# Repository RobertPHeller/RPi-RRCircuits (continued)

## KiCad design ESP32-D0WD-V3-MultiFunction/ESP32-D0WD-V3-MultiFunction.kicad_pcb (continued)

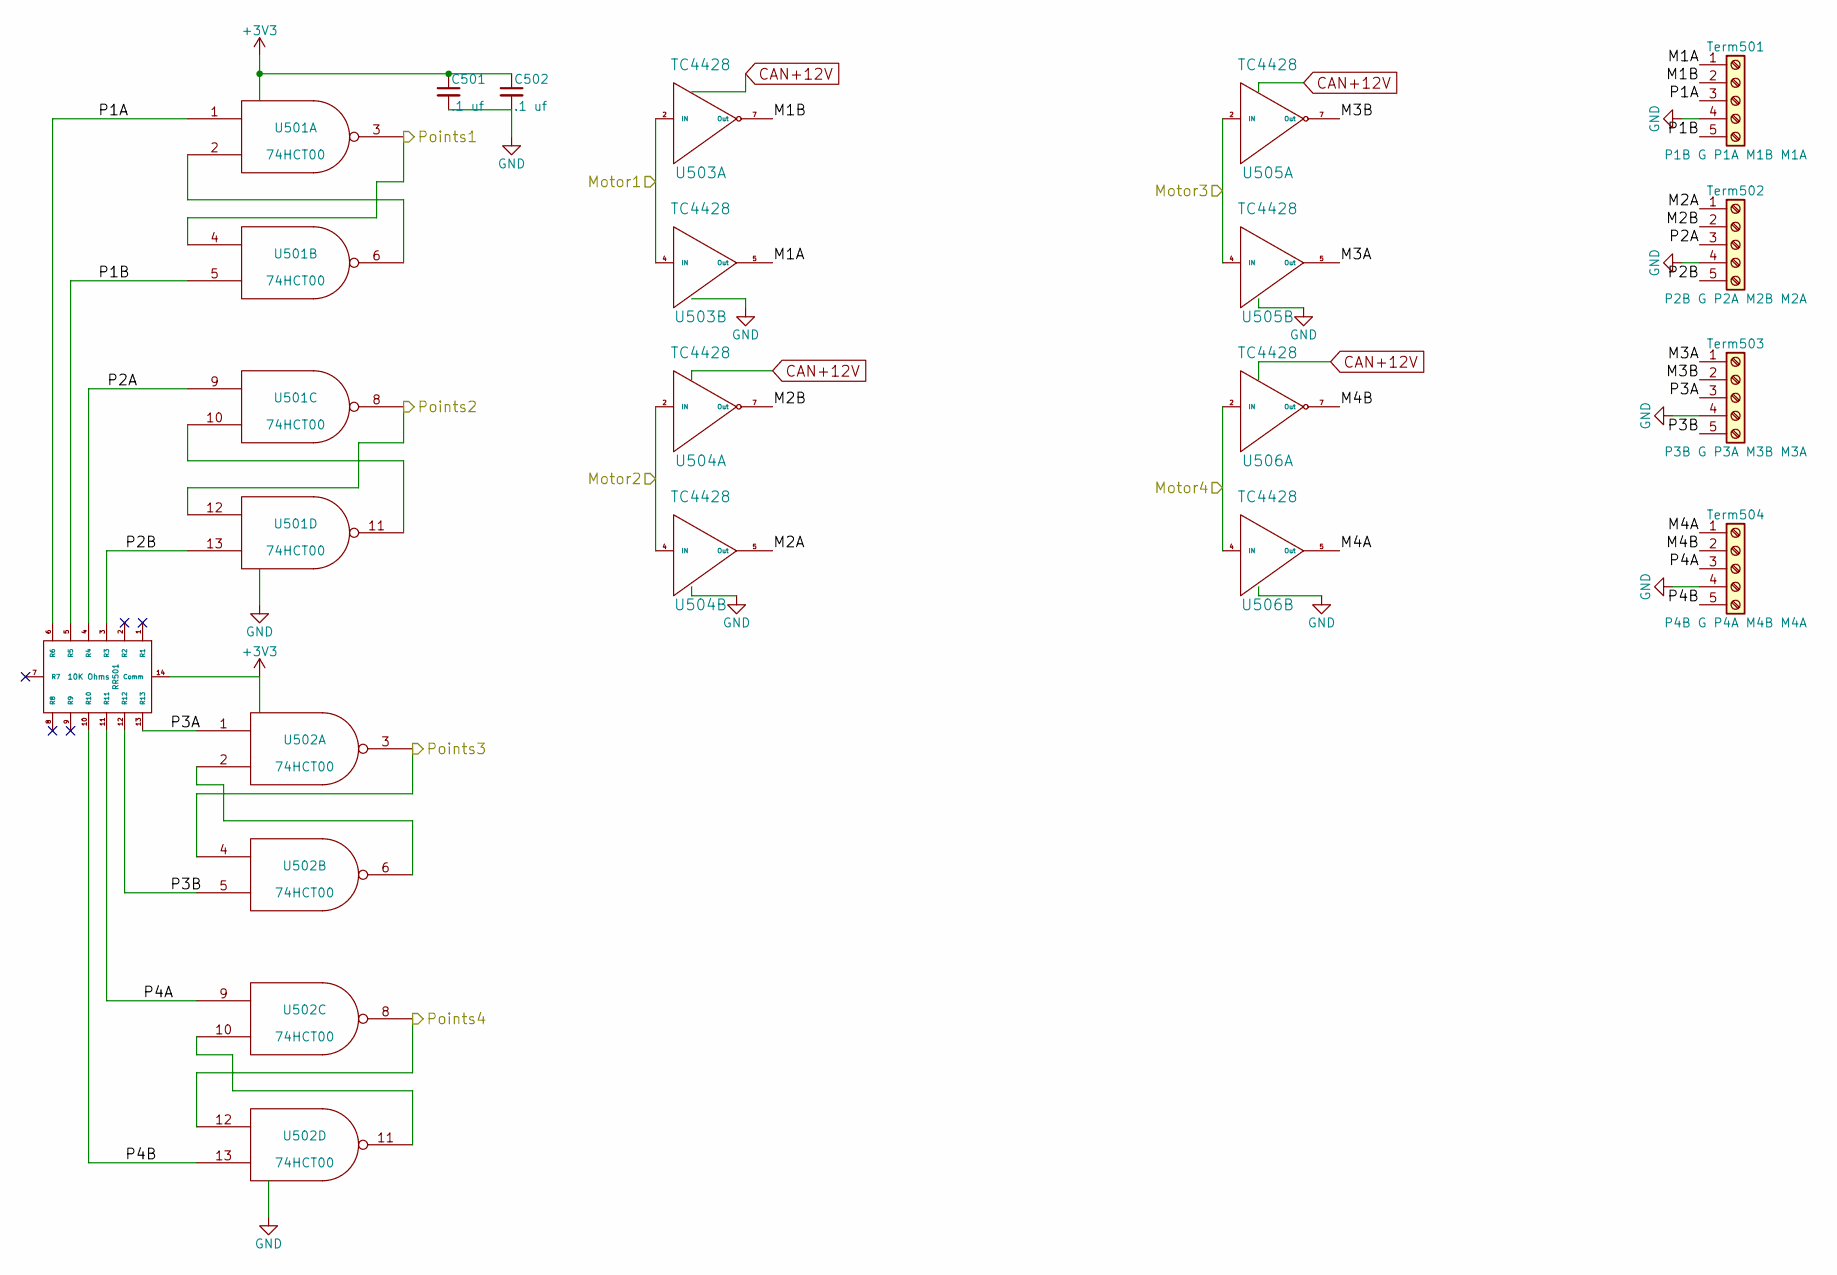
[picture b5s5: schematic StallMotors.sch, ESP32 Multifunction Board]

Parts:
C501, C502: .1 uf; C_0603; Mouser Part Number 710-885012206095
RR501: 10K Ohms; 4814P; Mouser Part Number 652-4814P-2LF-10K
Term501: P1B G P1A M1B M1A; TerminalBlock_Pheonix_MPT-2.54mm_5pol; Mouser Part Number 651-1725685
Term502: P2B G P2A M2B M2A; TerminalBlock_Pheonix_MPT-2.54mm_5pol; Mouser Part Number 651-1725685
Term503: P3B G P3A M3B M3A; TerminalBlock_Pheonix_MPT-2.54mm_5pol; Mouser Part Number 651-1725685
Term504: P4B G P4A M4B M4A; TerminalBlock_Pheonix_MPT-2.54mm_5pol; Mouser Part Number 651-1725685
U501: 74HCT00; SOIC-14_3.9x8.7mm_Pitch1.27mm
U502: 74HCT00; SOIC-14_3.9x8.7mm_Pitch1.27mm; Mouser Part Number 595-SN74AHC00D
U503, U504, U505, U506: TC4428; SOIC-8_3.9x4.9mm_Pitch1.27mm; Mouser Part Number 579-TC4428VOA

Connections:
/ESP32 MCU/GPIO12(Points1): U501.3, U501.4; also elsewhere on the board
/ESP32 MCU/GPIO13(Points2): U501.8, U501.12; also elsewhere on the board
/ESP32 MCU/GPIO14(Points3): U502.3, U502.4; also elsewhere on the board
/ESP32 MCU/GPIO25(Motor1): U503.2 (IN), U503.4 (IN); also elsewhere on the board
/ESP32 MCU/GPIO26(Motor2): U504.2 (IN), U504.4 (IN); also elsewhere on the board
/ESP32 MCU/GPIO27(Points4): U502.8, U502.12; also elsewhere on the board
/ESP32 MCU/GPIO32(Motor3): U505.2 (IN), U505.4 (IN); also elsewhere on the board
/ESP32 MCU/GPIO33(Motor4): U506.2 (IN), U506.4 (IN); also elsewhere on the board
/Stall Motors/M1A: Term501.1, U503.5 (Out)
/Stall Motors/M1B: Term501.2, U503.7 (Out)
/Stall Motors/M2A: Term502.1, U504.5 (Out)
/Stall Motors/M2B: Term502.2, U504.7 (Out)
/Stall Motors/M3A: Term503.1, U505.5 (Out)
/Stall Motors/M3B: Term503.2, U505.7 (Out)
/Stall Motors/M4A: Term504.1, U506.5 (Out)
/Stall Motors/M4B: Term504.2, U506.7 (Out)
/Stall Motors/P1A: RR501.6 (R6), Term501.3, U501.1
/Stall Motors/P1B: RR501.5 (R5), Term501.5, U501.5
/Stall Motors/P2A: RR501.4 (R4), Term502.3, U501.9
/Stall Motors/P2B: RR501.3 (R3), Term502.5, U501.13
/Stall Motors/P3A: RR501.13 (R13), Term503.3, U502.1
/Stall Motors/P3B: RR501.12 (R12), Term503.5, U502.5
/Stall Motors/P4A: RR501.11 (R11), Term504.3, U502.9
/Stall Motors/P4B: RR501.10 (R10), Term504.5, U502.13
CAN +12V: U503.6 (Vdd), U504.6 (Vdd), U505.6 (Vdd), U506.6 (Vdd); also elsewhere on the board
GND: C501.2, C502.2, Term501.4, Term502.4, Term503.4, Term504.4, U501.7 (GND), U502.7 (GND), U503.3 (GND), U504.3 (GND), U505.3 (GND), U506.3 (GND); also elsewhere on the board
unnamed: U501.2, U501.6
unnamed: U501.10, U501.11
unnamed: U502.2, U502.6
unnamed: U502.10, U502.11

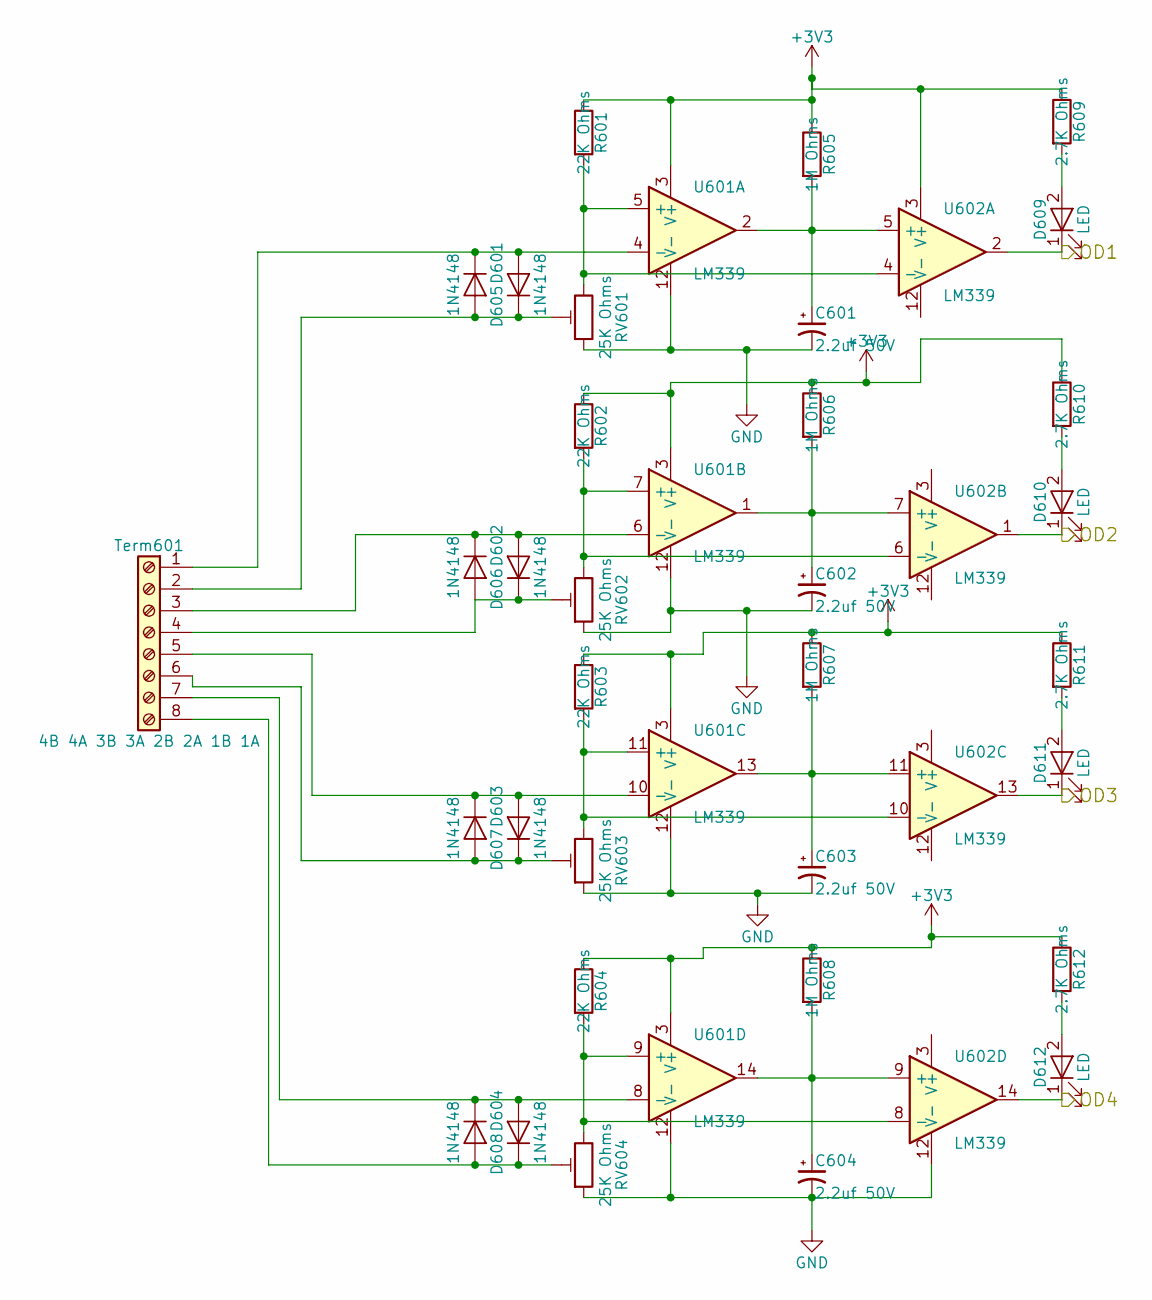
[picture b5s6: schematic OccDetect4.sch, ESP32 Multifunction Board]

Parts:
C601, C602, C603, C604: 2.2uf 50V; CP_Elec_4x5.7; Mouser Part Number 710-865080140002
D601, D602, D603, D604, D605, D606, D607, D608: 1N4148; D_SOD-123; Mouser Part Number 750-1N4148WS-HF
D609, D610, D611, D612: LED; LED_0603; Mouser Part Number 710-150060SS55040
R601, R602, R603, R604: 22K Ohms; R_0603; Mouser Part Number 71-RCG060322K0JNEA
R605, R606, R607, R608: 1M Ohms; R_0603; Mouser Part Number 71-CRCW06031M00JNEAC
R609, R610, R611, R612: 2.7K Ohms; R_0603; Mouser Part Number 71-CRCW06032K70JNEAC
RV601, RV602, RV603, RV604: 25K Ohms; Potentiometer_Trimmer_Bourns_3214J; Mouser Part Number 652-3314J-1-253E
Term601: 4B 4A 3B 3A 2B 2A 1B 1A; TerminalBlock_Pheonix_MPT-2.54mm_8pol; Mouser Part Number 651-1725711
U601, U602: LM339; SOIC-14_3.9x8.7mm_Pitch1.27mm; Mouser Part Number 595-LM339DR

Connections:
/ESP32 MCU/GPIO34(OD1): D609.1 (K), U602.2; also elsewhere on the board
/ESP32 MCU/GPIO35(OD2): D610.1 (K), U602.1; also elsewhere on the board
/ESP32 MCU/GPIO36(OD3): D611.1 (K), U602.13; also elsewhere on the board
/ESP32 MCU/GPIO39(OD4): D612.1 (K), U602.14; also elsewhere on the board
GND: C601.2, C602.2, C603.2, C604.2, RV601.1, RV602.1, RV603.1, RV604.1, U601.12 (V-), U602.12 (V-); also elsewhere on the board
unnamed: C601.1, R605.2, U601.2, U602.5 (+)
unnamed: C602.1, R606.2, U601.1, U602.7 (+)
unnamed: C603.1, R607.2, U601.13, U602.11 (+)
unnamed: C604.1, R608.2, U601.14, U602.9 (+)
unnamed: D601.1 (K), D605.2 (A), Term601.1, U601.4 (-)
unnamed: D601.2 (A), D605.1 (K), RV601.2, Term601.2
unnamed: D602.1 (K), D606.2 (A), Term601.3, U601.6 (-)
unnamed: D602.2 (A), D606.1 (K), RV602.2, Term601.4
unnamed: D603.1 (K), D607.2 (A), Term601.5, U601.10 (-)
unnamed: D603.2 (A), D607.1 (K), RV603.2, Term601.6
unnamed: D604.1 (K), D608.2 (A), Term601.7, U601.8 (-)
unnamed: D604.2 (A), D608.1 (K), RV604.2, Term601.8
unnamed: D609.2 (A), R609.2
unnamed: D610.2 (A), R610.2
unnamed: D611.2 (A), R611.2
unnamed: D612.2 (A), R612.2
unnamed: R601.2, RV601.3, U601.5 (+), U602.4 (-)
unnamed: R602.2, RV602.3, U601.7 (+), U602.6 (-)
unnamed: R603.2, RV603.3, U601.11 (+), U602.10 (-)
unnamed: R604.2, RV604.3, U601.9 (+), U602.8 (-)

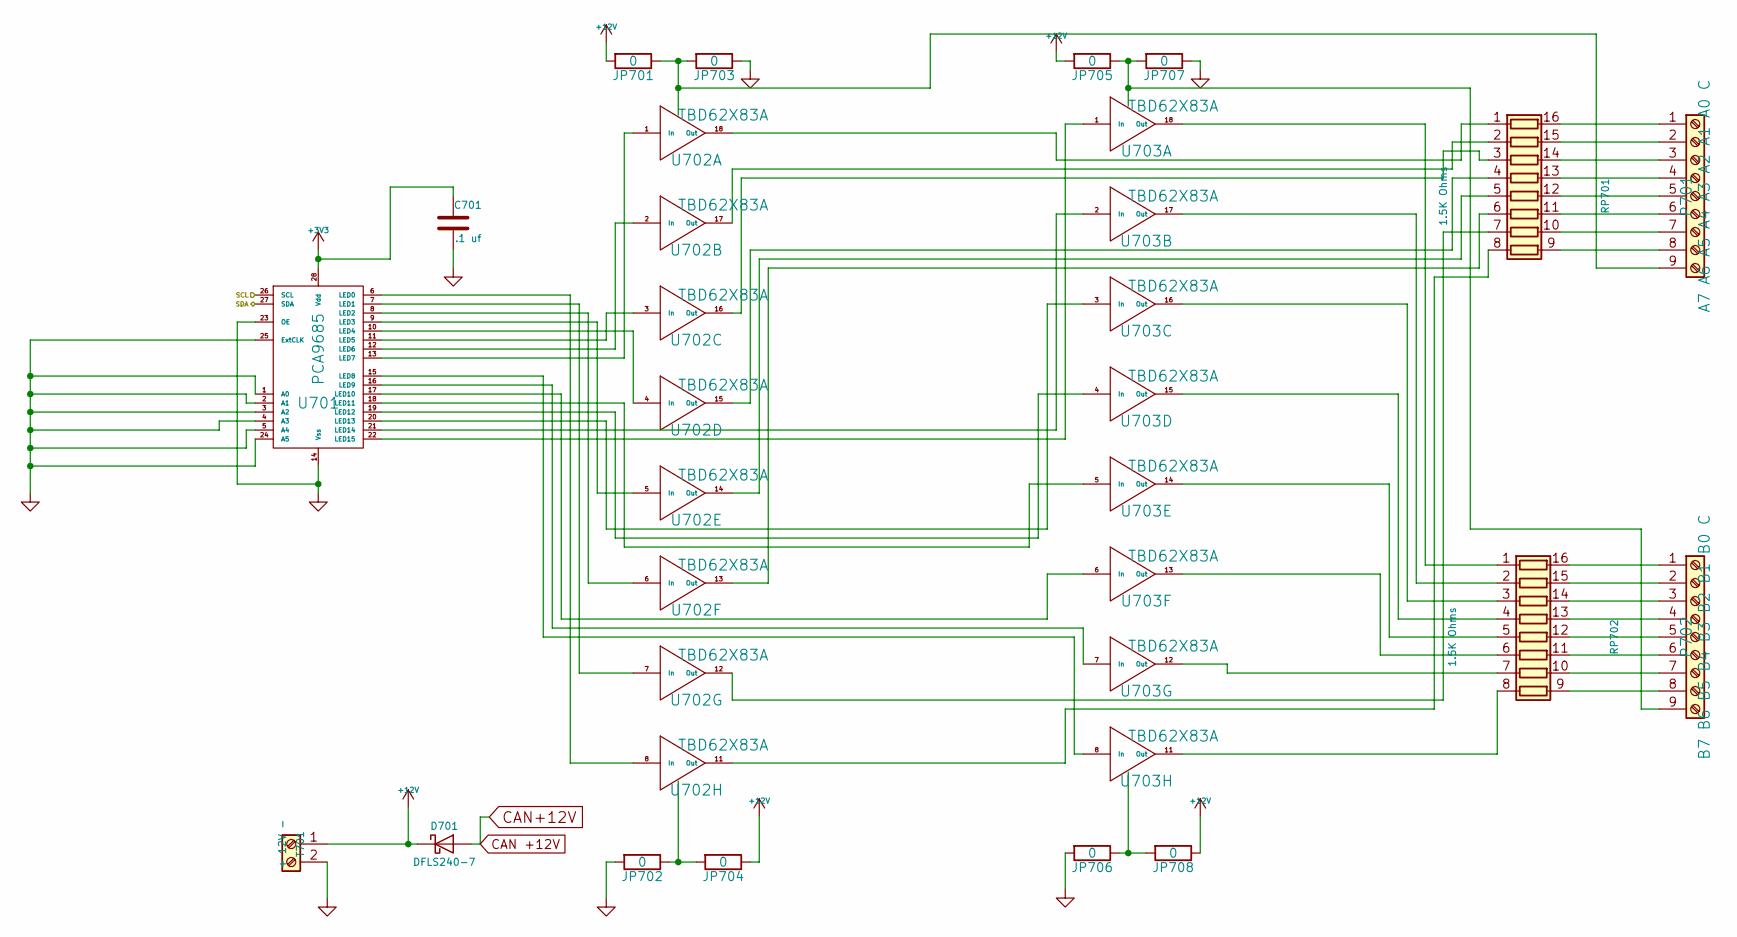
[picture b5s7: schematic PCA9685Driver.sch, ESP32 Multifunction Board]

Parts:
C701: .1 uf; C_0603; Mouser Part Number 710-885012206095
D701: DFLS240-7; D_PowerDI-123; Mouser Part Number 621-DFLS240-7
JP701, JP702, JP703, JP704, JP705, JP706, JP707, JP708: 0; R_1206; Mouser Part Number 71-CRCW12060000Z0EBC
P701: A7 A6 A5 A4 A3 A2 A1 A0 C; TerminalBlock_Pheonix_MPT-2.54mm_9pol; Mouser Part Number 651-1725724
P702: B7 B6 B5 B4 B3 B2 B1 B0 C; TerminalBlock_Pheonix_MPT-2.54mm_9pol; Mouser Part Number 651-1725724
RP701, RP702: 1.5K Ohms; 4816P; Mouser Part Number 652-4816P-T1LF-1.5K
T701: + 12V -; TerminalBlock_Pheonix_MPT-2.54mm_2pol; Mouser Part Number 651-1725656
U701: PCA9685; TSSOP-28_4.4x9.7mm_Pitch0.65mm; Mouser Part Number 771-PCA9685PW,118
U702, U703: TBD62X83A; SOIC-18W_7.5x11.6mm_Pitch1.27mm; Mouser Part Number 757-TBD62083AFG or 757-TBD62783AFG

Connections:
+12V: D701.1 (K), JP701.2, JP704.1, JP705.2, JP708.1, T701.1
/ESP32 MCU/SCL: U701.26 (SCL); also elsewhere on the board
/ESP32 MCU/SDA: U701.27 (SDA); also elsewhere on the board
CAN +12V: D701.2 (A); also elsewhere on the board
GND: C701.2, JP702.2, JP703.1, JP706.2, JP707.1, T701.2, U701.1 (A0), U701.2 (A1), U701.3 (A2), U701.4 (A3), U701.5 (A4), U701.14 (Vss), U701.23 (OE), U701.24 (A5), U701.25 (ExtCLK); also elsewhere on the board
unnamed: JP701.1, JP703.2, P701.9, U702.10 (OC)
unnamed: JP702.1, JP704.2, U702.9 (IC)
unnamed: JP705.1, JP707.2, P702.9, U703.10 (OC)
unnamed: JP706.1, JP708.2, U703.9 (IC)
unnamed: P701.1, RP701.16 (R1.2)
unnamed: P701.2, RP701.15 (R2.2)
unnamed: P701.3, RP701.14 (R3.2)
unnamed: P701.4, RP701.13 (R4.2)
unnamed: P701.5, RP701.12 (R5.2)
unnamed: P701.6, RP701.11 (R6.2)
unnamed: P701.7, RP701.10 (R7.2)
unnamed: P701.8, RP701.9 (R8.2)
unnamed: P702.1, RP702.16 (R1.2)
unnamed: P702.2, RP702.15 (R2.2)
unnamed: P702.3, RP702.14 (R3.2)
unnamed: P702.4, RP702.13 (R4.2)
unnamed: P702.5, RP702.12 (R5.2)
unnamed: P702.6, RP702.11 (R6.2)
unnamed: P702.7, RP702.10 (R7.2)
unnamed: P702.8, RP702.9 (R8.2)
unnamed: RP701.1 (R1.1), U702.18 (Out)
unnamed: RP701.2 (R2.1), U702.17 (Out)
unnamed: RP701.3 (R3.1), U702.16 (Out)
unnamed: RP701.4 (R4.1), U702.15 (Out)
unnamed: RP701.5 (R5.1), U702.14 (Out)
unnamed: RP701.6 (R6.1), U702.13 (Out)
unnamed: RP701.7 (R7.1), U702.12 (Out)
unnamed: RP701.8 (R8.1), U702.11 (Out)
unnamed: RP702.1 (R1.1), U703.18 (Out)
unnamed: RP702.2 (R2.1), U703.17 (Out)
unnamed: RP702.3 (R3.1), U703.16 (Out)
unnamed: RP702.4 (R4.1), U703.15 (Out)
unnamed: RP702.5 (R5.1), U703.14 (Out)
unnamed: RP702.6 (R6.1), U703.13 (Out)
unnamed: RP702.7 (R7.1), U703.12 (Out)
unnamed: RP702.8 (R8.1), U703.11 (Out)
unnamed: U701.6 (LED0), U702.8 (In)
unnamed: U701.7 (LED1), U702.7 (In)
unnamed: U701.8 (LED2), U702.6 (In)
unnamed: U701.9 (LED3), U702.5 (In)
unnamed: U701.10 (LED4), U702.4 (In)
unnamed: U701.11 (LED5), U702.3 (In)
unnamed: U701.12 (LED6), U702.2 (In)
unnamed: U701.13 (LED7), U702.1 (In)
unnamed: U701.15 (LED8), U703.8 (In)
unnamed: U701.16 (LED9), U703.7 (In)
unnamed: U701.17 (LED10), U703.6 (In)
unnamed: U701.18 (LED11), U703.5 (In)
unnamed: U701.19 (LED12), U703.4 (In)
unnamed: U701.20 (LED13), U703.3 (In)
unnamed: U701.21 (LED14), U703.2 (In)
unnamed: U701.22 (LED15), U703.1 (In)

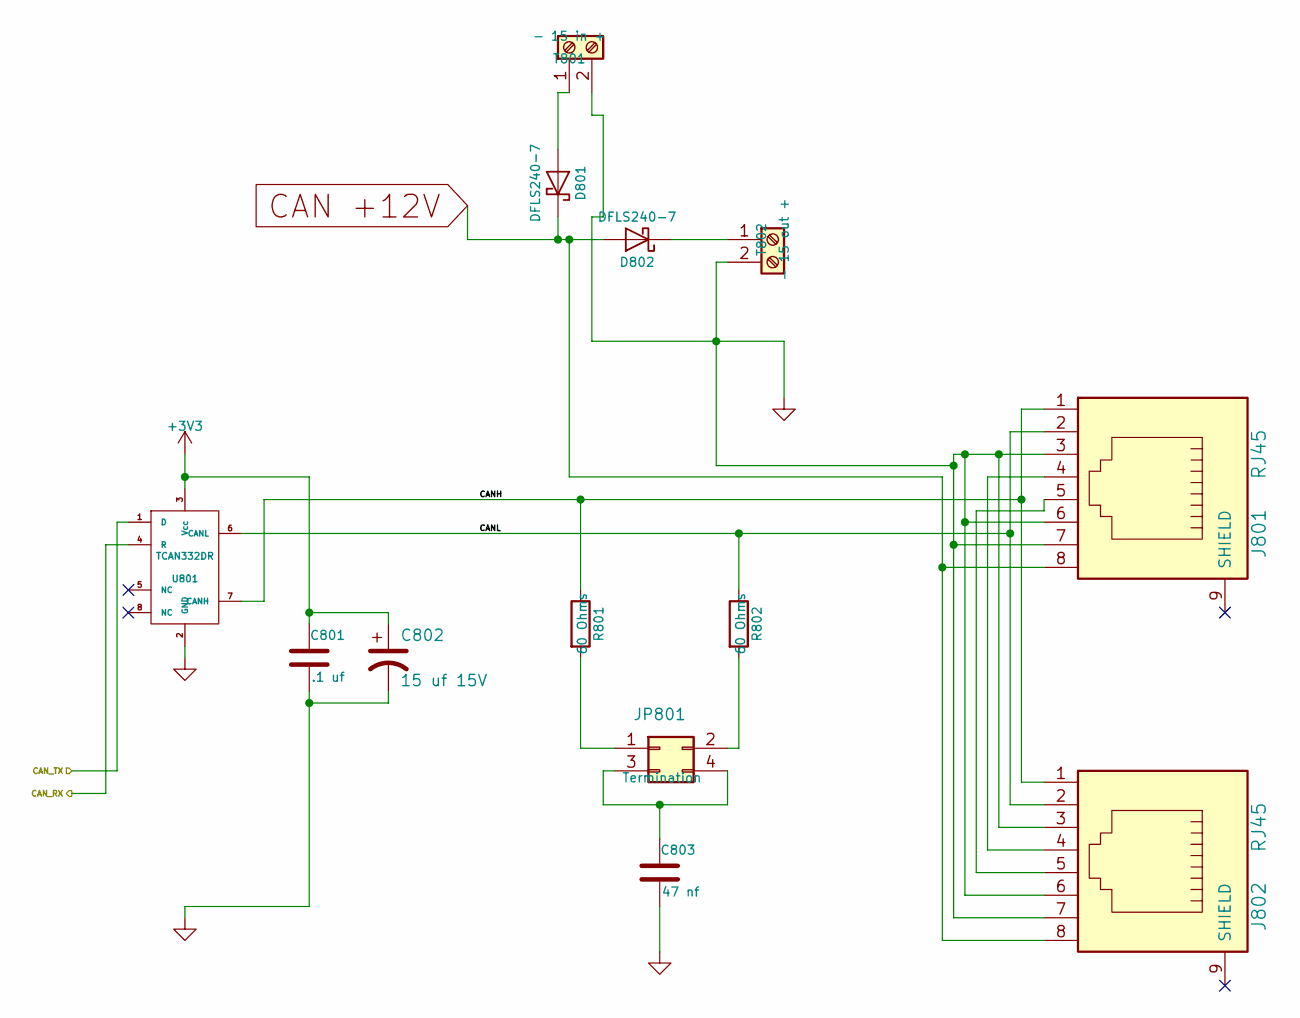
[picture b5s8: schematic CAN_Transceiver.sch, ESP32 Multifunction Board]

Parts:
C801: .1 uf; C_0603; Mouser Part Number 710-885012206095
C802: 15 uf 15V; CP_Elec_4x5.7; Mouser Part Number 647-UUD1C150MCL
C803: 47 nf; C_0603; Mouser Part Number 710-885012206093
D801, D802: DFLS240-7; D_PowerDI-123; Mouser Part Number 621-DFLS240-7
J801, J802: RJ45; RJ45_8N-S; Mouser Part Number 710-615008144221
JP801: Termination; Pin_Header_Straight_2x02_Pitch2.54mm; Mouser Part Number 649-67997-404HLF
R801, R802: 60 Ohms; R_1206; Mouser Part Number 71-CRCW120660R0KNAIF
T801: - 15 in +; TerminalBlock_Pheonix_MPT-2.54mm_2pol; Mouser Part Number 651-1725656
T802: - 15 out +; TerminalBlock_Pheonix_MPT-2.54mm_2pol; Mouser Part Number 651-1725656
U801: TCAN332DR; SOIC-8_3.9x4.9mm_Pitch1.27mm; Mouser Part Number 595-TCAN332DR

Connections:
/CAN Tranceiver/CANH: J801.1, J802.1, R801.1, U801.7 (CANH)
/CAN Tranceiver/CANL: J801.2, J802.2, R802.1, U801.6 (CANL)
/CAN Tranceiver/CAN_RX: U801.4 (R); also elsewhere on the board
/CAN Tranceiver/CAN_TX: U801.1 (D); also elsewhere on the board
CAN +12V: D801.1 (K), D802.2 (A), J801.8, J802.8; also elsewhere on the board
GND: C801.2, C802.2, C803.2, J801.3, J801.6, J801.7, J802.3, J802.6, J802.7, T801.2, T802.2, U801.2 (GND); also elsewhere on the board
unnamed: C803.1, JP801.3, JP801.4
unnamed: D801.2 (A), T801.1
unnamed: D802.1 (K), T802.1
unnamed: J801.4, J802.4
unnamed: J801.5, J802.5
unnamed: JP801.1, R801.2
unnamed: JP801.2, R802.2

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
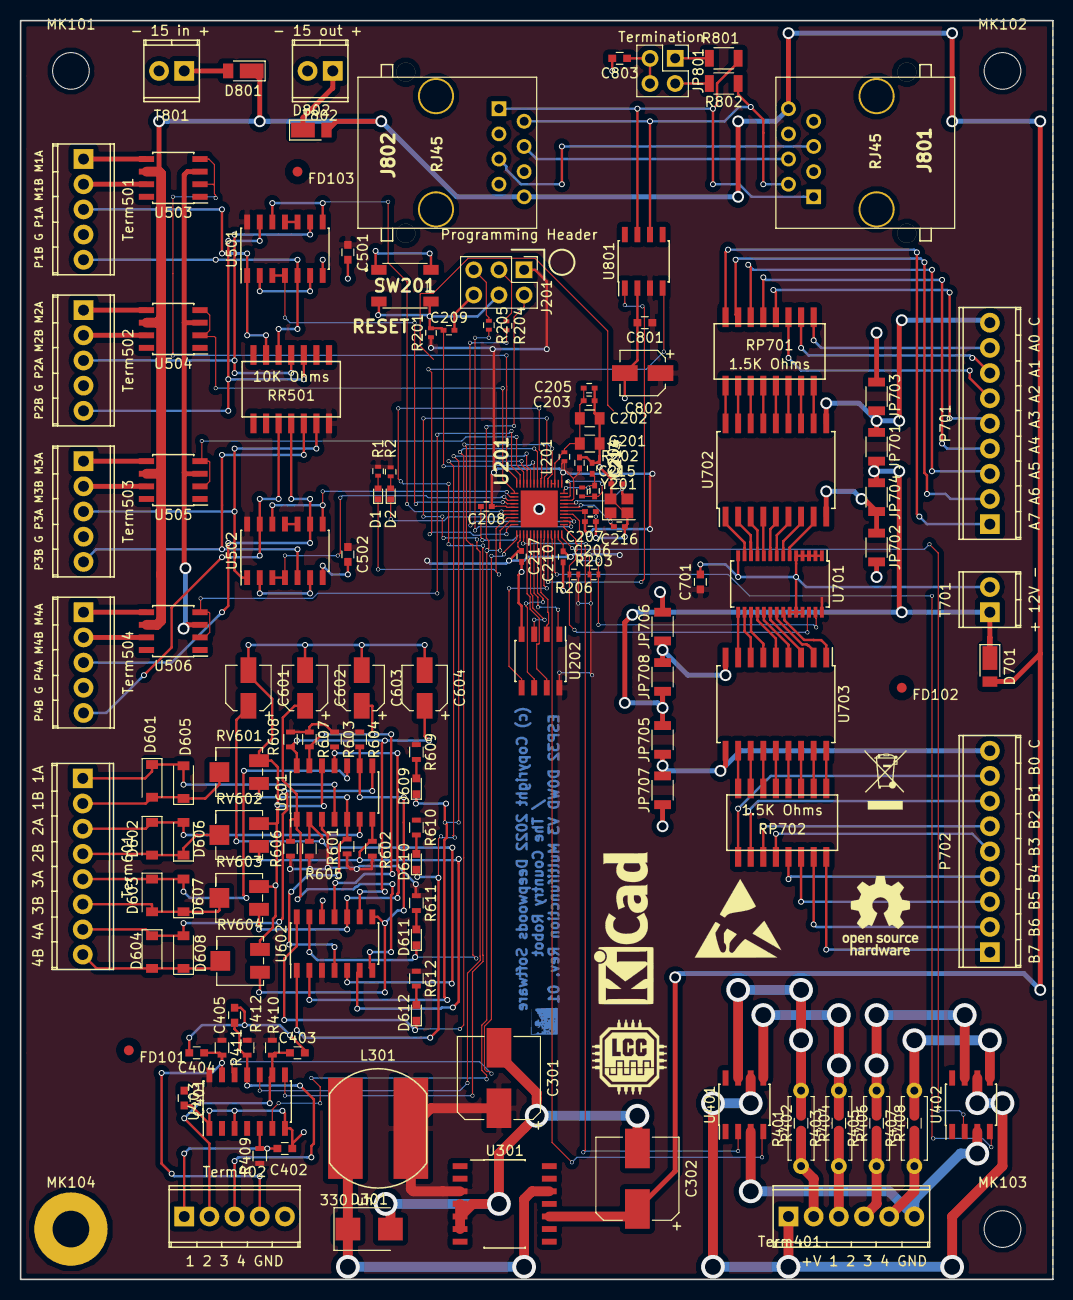
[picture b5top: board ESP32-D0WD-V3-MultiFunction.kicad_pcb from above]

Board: 2 copper layers, 104.1 x 127.0 mm, 144 parts (0 on the bottom side), 163 nets.

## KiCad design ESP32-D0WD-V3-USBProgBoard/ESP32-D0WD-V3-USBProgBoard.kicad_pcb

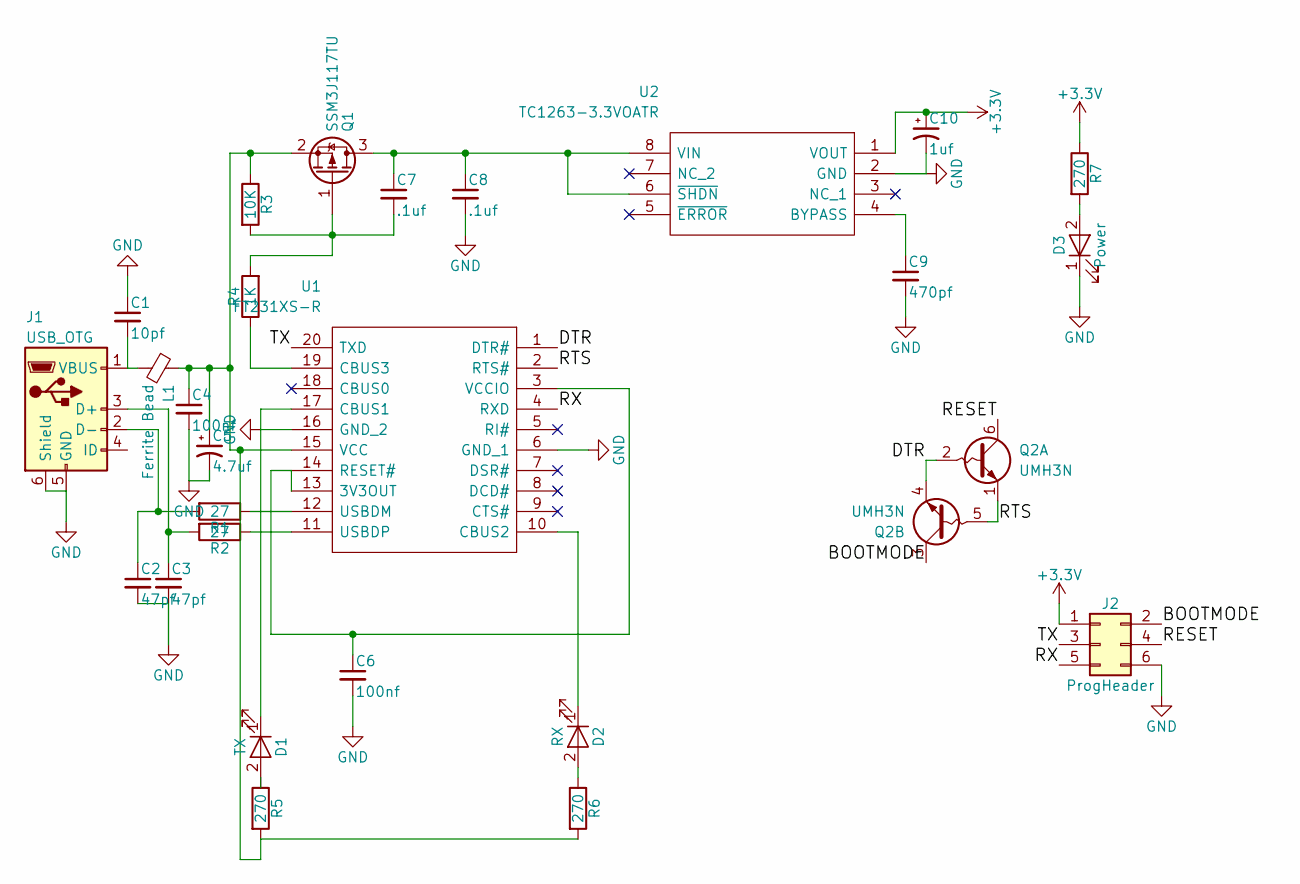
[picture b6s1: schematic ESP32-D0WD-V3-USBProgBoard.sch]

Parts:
C1: 10pf; C_0402; Mouser Part Number 80-C0402C100K5RAUTO
C2, C3: 47pf; C_0402; Mouser Part Number 80-C0402C470K5RAUTO
C4, C6: 100nf; C_0402; Mouser Part Number 80-C0402C104K8R
C5: 4.7uf; CP_Elec_4x5.7; Mouser Part Number 710-865080540002
C7, C8: .1uf; C_0402; Mouser Part Number 80-C0402C104K8R
C9: 470pf; C_0402; Mouser Part Number 80-C0402S471K3RAUTO
C10: 1uf; CP_Elec_4x4.5; Mouser Part Number 647-UZG1H010MCL1GB
D1: TX; LED_0402; Mouser Part Number 710-150040GS73220
D2: RX; LED_0402; Mouser Part Number 710-150040SS73220
D3: Power; LED_0402; Mouser Part Number 710-150040AS73220
J1: USB_OTG; USB_Micro-B_Molex_47346-0001; Mouser Part Number 538-47346-0001
J2: ProgHeader; Socket_Strip_Straight_2x03_Pitch2.54mm
L1: Ferrite Bead; L_0402; Mouser Part Number 810-MMZ1005S800CTD25
Q1: SSM3J117TU; SOTFL65P210X75-3N; Mouser Part Number 757-SSM3J117TULF
Q2: UMH3N; SOT-363_SC-70-6; Mouser Part Number 755-UMH3NFHATN
R1, R2: 27; R_0402; Mouser Part Number 603-RT0402FRE0727RL
R3: 10K; R_0402; Mouser Part Number 603-AT0402FRE0710KL
R4: 1K; R_0402; Mouser Part Number 603-RT0402FRE071KL
R5, R6, R7: 270; R_0402; Mouser Part Number 754-RR0510P-271D
U1: FT231XS-R; SSOP-20_5.3x7.2mm_Pitch0.65mm; Manufacturer_Part_Number FT231XS-R
U2: TC1263-3.3VOATR; SO-8_5.3x6.2mm_Pitch1.27mm; Manufacturer_Part_Number TC1263-3.3VOATR

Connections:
+3V3: C10.1, J2.1, R7.1, U2.1 (VOUT)
/BOOTMODE: J2.2, Q2.3 (C2)
/DTR: Q2.2 (B1), Q2.4 (E2), U1.1 (DTR#)
/RESET: J2.4, Q2.6 (C1)
/RTS: Q2.1 (E1), Q2.5 (B2), U1.2 (RTS#)
/RX: J2.5, U1.4 (RXD)
/TX: J2.3, U1.20 (TXD)
unnamed: C1.2, J1.1 (VBUS), L1.2
unnamed: C2.1, J1.2 (D-), R1.2
unnamed: C3.1, J1.3 (D+), R2.2
unnamed: C4.1, C5.1, L1.1, Q1.2 (S), R3.1, R5.2, R6.2, U1.15 (VCC)
unnamed: C6.1, U1.3 (VCCIO), U1.13 (3V3OUT), U1.14 (RESET#)
unnamed: C7.1, C8.1, Q1.3 (D), U2.6 (~SHDN), U2.8 (VIN)
unnamed: C7.2, Q1.1 (G), R3.2, R4.2
unnamed: C9.1, U2.4 (BYPASS)
unnamed: D1.2 (A), R5.1
unnamed: D2.1 (K), U1.10 (CBUS2)
unnamed: D2.2 (A), R6.1
unnamed: D3.2 (A), R7.2
unnamed: R1.1, U1.12 (USBDM)
unnamed: R2.1, U1.11 (USBDP)
unnamed: R4.1, U1.19 (CBUS3)

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
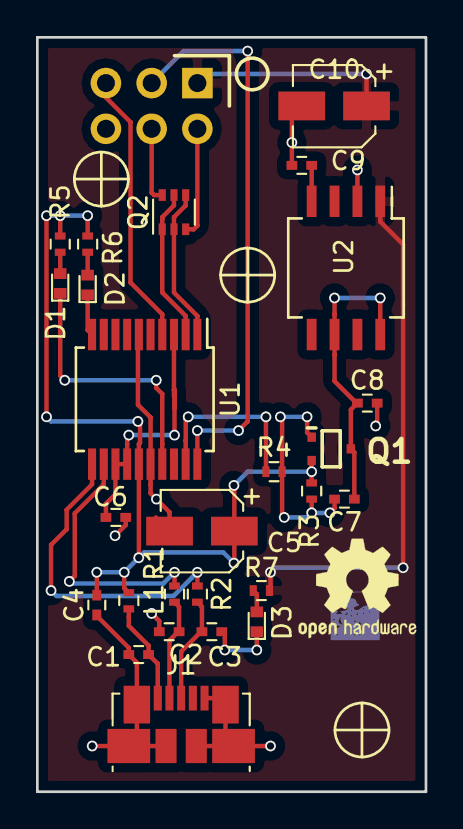
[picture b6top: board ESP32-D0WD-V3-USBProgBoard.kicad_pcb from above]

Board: 2 copper layers, 21.6 x 41.9 mm, 27 parts (1 on the bottom side), 24 nets.

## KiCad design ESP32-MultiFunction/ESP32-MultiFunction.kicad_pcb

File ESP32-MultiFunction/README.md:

# ESP32-MultiFunction

This is a circuit board that supports an ESP32 Dev Kit board or TTGO-T1 board
to manage a range of possible interlocking plants or other model railroad
situations. It contains four stall motor drivers with point sense, four CT
Coil type occupancy detectors, four Schmitt-Trigger inputs (for push buttons),
four driver outputs, and 16 PWM LED drivers.

The board contains these I/O sections:

- Four occupancy detectors.  These are current transformer based for DCC.
- Four stall-motor with point sense.
- Four Schmitt-Trigger inputs, typically for facia push buttons
- Four driver outputs, typically for facia lamps (LEDs).
- Sixteen PWM Led drivers.  These are meant to light lamps in signal heads. 

This board uses 16 GPIO pins and one I2C channel:

- **GPIO34** Occupancy Detector 1.
- **GPIO35** Occupancy Detector 2.
- **GPIO36** Occupancy Detector 3.
- **GPIO39** Occupancy Detector 4.
- **GPIO25** Motor Select 1: select the position of stall motor 1.
- **GPIO26** Motor Select 1: select the position of stall motor 2.
- **GPIO32** Motor Select 1: select the position of stall motor 3.
- **GPIO33** Motor Select 1: select the position of stall motor 4.
- **GPIO12** Point Sense 1: return the state of the points for stall motor 1.
- **GPIO13** Point Sense 1: return the state of the points for stall motor 2.
- **GPIO14** Point Sense 1: return the state of the points for stall motor 3.
- **GPIO27** Point Sense 1: return the state of the points for stall motor 4.
- **GPIO0** Schmitt trigger input 1.
- **GPIO2** Schmitt trigger input 2.
- **GPIO15** Schmitt trigger input 3.
- **GPIO16** Schmitt trigger input 4.
- **GPIO17** Driver (LED) 1.
- **GPIO18** Driver (LED) 2.
- **GPIO19** Driver (LED) 3.
- **GPIO23** Driver (LED) 4.
- **I2C Address 0x40** A PCA9685 16-channel, 12-bit PWM LED Controller

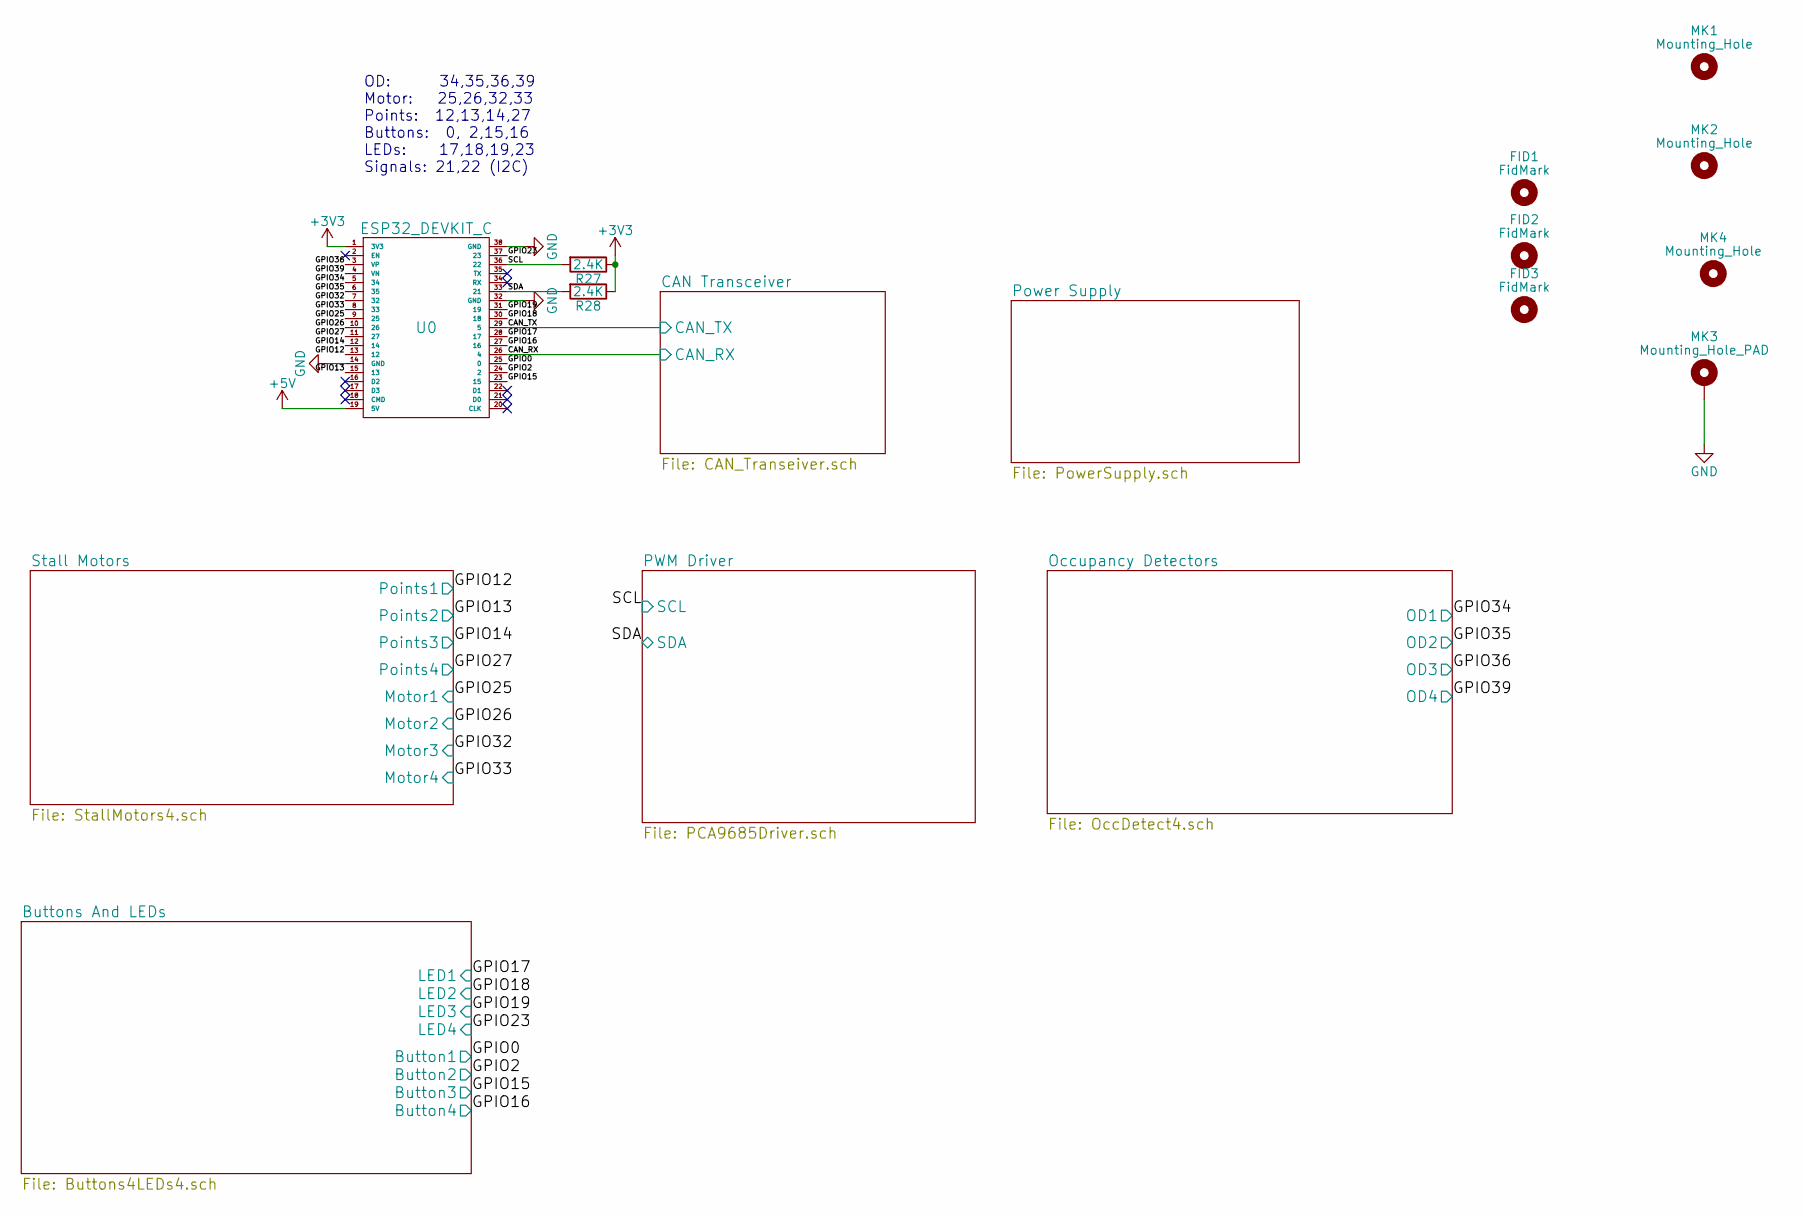
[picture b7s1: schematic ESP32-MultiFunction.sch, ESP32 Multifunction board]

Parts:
FID1, FID2, FID3: FidMark; Fiducial_1mm_Dia_2.54mm_Outer_CopperBottom
MK1, MK2, MK4: Mounting_Hole; MountingHole_3.2mm_M3
MK3: Mounting_Hole_PAD; MountingHole_3.2mm_M3_Pad
R27, R28: 2.4K; R_0603; Mouser Part Number 71-CRCW06032K40JN
U0: ESP32_DEVKIT_C; ESP32-Combo

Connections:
+3V3: R27.1, R28.1, U0.1 (3V3); also elsewhere on the board
+5V: U0.19 (5V); also elsewhere on the board
/CAN_RX: U0.26 (4); also elsewhere on the board
/CAN_TX: U0.29 (5); also elsewhere on the board
/GPIO0: U0.25 (0); also elsewhere on the board
/GPIO2: U0.24 (2); also elsewhere on the board
/GPIO12: U0.13 (12); also elsewhere on the board
/GPIO13: U0.15 (13); also elsewhere on the board
/GPIO14: U0.12 (14); also elsewhere on the board
/GPIO15: U0.23 (15); also elsewhere on the board
/GPIO16: U0.27 (16); also elsewhere on the board
/GPIO17: U0.28 (17); also elsewhere on the board
/GPIO18: U0.30 (18); also elsewhere on the board
/GPIO19: U0.31 (19); also elsewhere on the board
/GPIO23: U0.37 (23); also elsewhere on the board
/GPIO25: U0.9 (25); also elsewhere on the board
/GPIO26: U0.10 (26); also elsewhere on the board
/GPIO27: U0.11 (27); also elsewhere on the board
/GPIO32: U0.7 (32); also elsewhere on the board
/GPIO33: U0.8 (33); also elsewhere on the board
/GPIO34: U0.5 (34); also elsewhere on the board
/GPIO35: U0.6 (35); also elsewhere on the board
/GPIO36: U0.3 (VP); also elsewhere on the board
/GPIO39: U0.4 (VN); also elsewhere on the board
/SCL: R27.2, U0.36 (22); also elsewhere on the board
/SDA: R28.2, U0.33 (21); also elsewhere on the board
GND: MK3.1, U0.14 (GND), U0.32 (GND), U0.38 (GND); also elsewhere on the board

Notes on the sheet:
OD: 34,35,36,39 Motor: 25,26,32,33 Points: 12,13,14,27 Buttons: 0, 2,15,16 LEDs: 17,18,19,23 Signals: 21,22 (I2C)

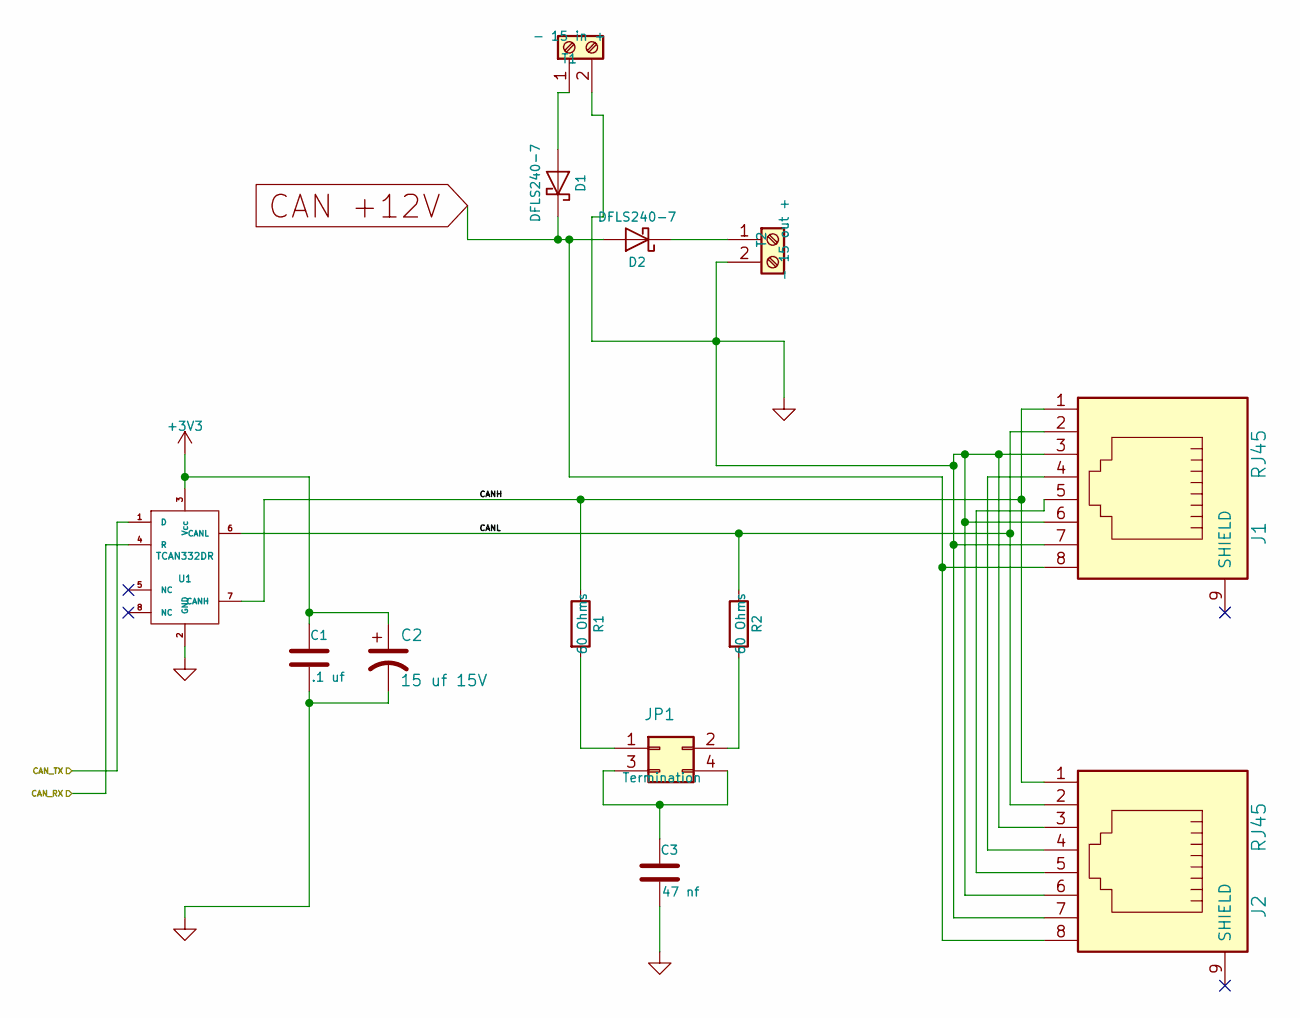
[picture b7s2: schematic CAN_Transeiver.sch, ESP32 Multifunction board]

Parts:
C1: .1 uf; C_0603; Mouser Part Number 710-885012206095
C2: 15 uf 15V; CP_Elec_4x5.7; Mouser Part Number 647-UUD1C150MCL
C3: 47 nf; C_0603; Mouser Part Number 710-885012206093
D1, D2: DFLS240-7; D_SMB; Mouser Part Number 621-DFLS240-7
J1, J2: RJ45; RJ45_8N-S; Mouser Part Number 710-615008144221
JP1: Termination; Pin_Header_Straight_2x02_Pitch2.54mm; Mouser Part Number 649-67997-404HLF
R1, R2: 60 Ohms; R_1206; Mouser Part Number 71-CRCW120660R0KNAIF
T1: - 15 in +; TerminalBlock_Pheonix_MPT-2.54mm_2pol; Mouser Part Number 651-1725656
T2: - 15 out +; TerminalBlock_Pheonix_MPT-2.54mm_2pol; Mouser Part Number 651-1725656
U1: TCAN332DR; SOIC-8_3.9x4.9mm_Pitch1.27mm; Mouser Part Number 595-TCAN332DR

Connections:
+3V3: C1.1, C2.1, U1.3 (Vcc); also elsewhere on the board
/CAN Transceiver/CANH: J1.1, J2.1, R1.1, U1.7 (CANH)
/CAN Transceiver/CANL: J1.2, J2.2, R2.1, U1.6 (CANL)
/CAN_RX: U1.4 (R); also elsewhere on the board
/CAN_TX: U1.1 (D); also elsewhere on the board
CAN +12V: D1.1 (K), D2.2 (A), J1.8, J2.8; also elsewhere on the board
GND: C1.2, C2.2, C3.2, J1.3, J1.6, J1.7, J2.3, J2.6, J2.7, T1.2, T2.2, U1.2 (GND); also elsewhere on the board
unnamed: C3.1, JP1.3, JP1.4
unnamed: D1.2 (A), T1.1
unnamed: D2.1 (K), T2.1
unnamed: J1.4, J2.4
unnamed: J1.5, J2.5
unnamed: JP1.1, R1.2
unnamed: JP1.2, R2.2
